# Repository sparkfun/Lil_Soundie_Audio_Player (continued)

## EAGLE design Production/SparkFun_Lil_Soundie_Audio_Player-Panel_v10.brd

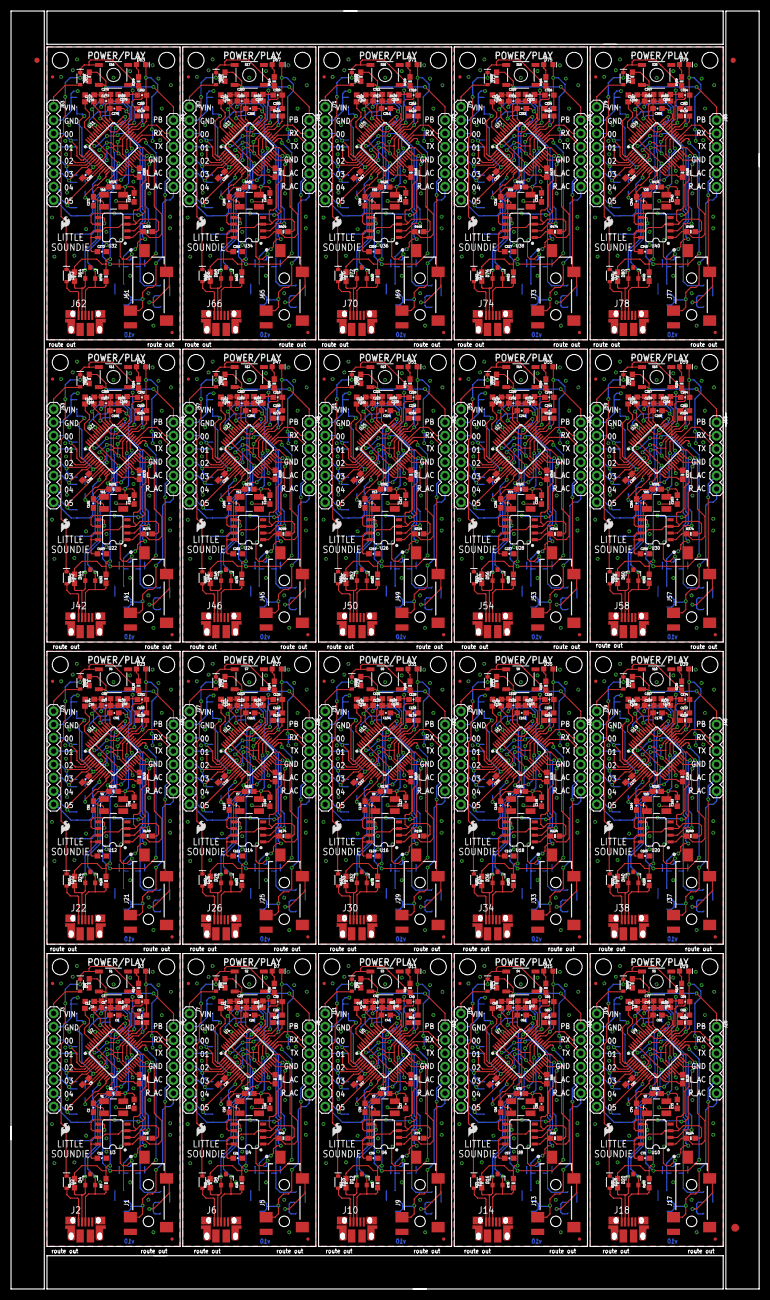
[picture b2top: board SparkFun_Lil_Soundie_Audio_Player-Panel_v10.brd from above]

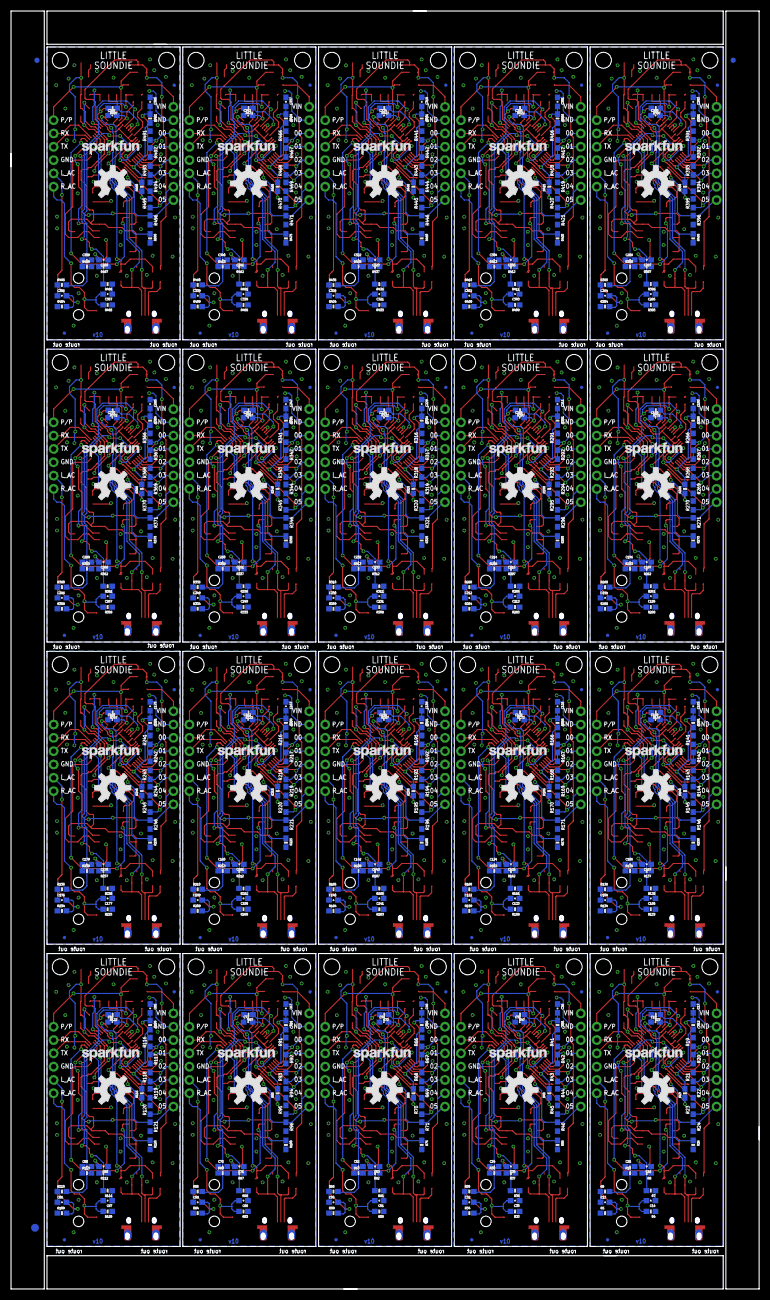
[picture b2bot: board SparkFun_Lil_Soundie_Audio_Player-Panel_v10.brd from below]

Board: 2 copper layers, 142.7 x 243.8 mm, 1286 parts (523 on the bottom side), 800 nets.

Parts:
C1, C2, C18, C20, C37, C38, C55, C56, C73, C74, C91, C92, C109, C110, C127, C128, C145, C146, C163, C164, C181, C182, C199, C200, C217, C218, C235, C236, C253, C254, C271, C272, C289, C290, C307, C308, C325, C326, C343, C344: 22pF; 0603-CAP
C3, C13, C14, C17, C23, C31, C32, C33, C41, C49, C50, C51, C59, C67, C68, C69, C77, C85, C86, C87, C95, C103, C104, C105, C113, C121, C122, C123, C131, C139, C140, C141, C149, C157, C158, C159, C167, C175, C176, C177, C185, C193, C194, C195, C203, C211, C212, C213, C221, C229, C230, C231, C239, C247, C248, C249, C257, C265, C266, C267, C275, C283, C284, C285, C293, C301, C302, C303, C311, C319, C320, C321, C329, C337, C338, C339, C347, C355, C356, C357: 10uF; 0603-CAP
C4, C5, C6, C7, C8, C9, C12, C21, C24, C25, C26, C27, C28, C29, C39, C42, C43, C44, C45, C46, C47, C57, C60, C61, C62, C63, C64, C65, C75, C78, C79, C80, C81, C82, C83, C93, C96, C97, C98, C99, C100, C101, C111, C114, C115, C116, C117, C118, C119, C129, C132, C133, C134, C135, C136, C137, C147, C150, C151, C152, C153, C154, C155, C165, C168, C169, C170, C171, C172, C173, C183, C186, C187, C188, C189, C190, C191, C201, C204, C205, C206, C207, C208, C209, C219, C222, C223, C224, C225, C226, C227, C237, C240, C241, C242, C243, C244, C245, C255, C258, C259, C260, C261, C262, C263, C273, C276, C277, C278, C279, C280, C281, C291, C294, C295, C296, C297, C298, C299, C309, C312, C313, C314, C315, C316, C317, C327, C330, C331, C332, C333, C334, C335, C345, C348, C349, C350, C351, C352, C353: 0.1uF; 0603-CAP
C10, C11, C22, C30, C40, C48, C58, C66, C76, C84, C94, C102, C112, C120, C130, C138, C148, C156, C166, C174, C184, C192, C202, C210, C220, C228, C238, C246, C256, C264, C274, C282, C292, C300, C310, C318, C328, C336, C346, C354: 1.0uF; 0603-CAP
C15, C16, C34, C35, C52, C53, C70, C71, C88, C89, C106, C107, C124, C125, C142, C143, C160, C161, C178, C179, C196, C197, C214, C215, C232, C233, C250, C251, C268, C269, C286, C287, C304, C305, C322, C323, C340, C341, C358, C359: 10nF; 0603-CAP
C19, C36, C54, C72, C90, C108, C126, C144, C162, C180, C198, C216, C234, C252, C270, C288, C306, C324, C342, C360: 47nF; 0603-CAP
D1, D2, D5, D6, D9, D10, D13, D14, D17, D18, D21, D22, D25, D26, D29, D30, D33, D34, D37, D38, D41, D42, D45, D46, D49, D50, D53, D54, D57, D58, D61, D62, D65, D66, D69, D70, D73, D74, D77, D78: 1A/23V/620mV; SOD-323
D3, D7, D11, D15, D19, D23, D27, D31, D35, D39, D43, D47, D51, D55, D59, D63, D67, D71, D75, D79: RED; LED-0603
D4, D8, D12, D16, D20, D24, D28, D32, D36, D40, D44, D48, D52, D56, D60, D64, D68, D72, D76, D80: PESD1CAN; SOT23-3
E$1, E$2, E$6, E$7: FIDUCIAL-1X2
E$3, E$4: FIDUCIAL-1.5X3
FD1, FD2, FD3, FD4, FD5, FD6, FD7, FD8, FD9, FD10, FD11, FD12, FD13, FD14, FD15, FD16, FD17, FD18, FD19, FD20, FD21, FD22, FD23, FD24, FD25, FD26, FD27, FD28, FD29, FD30, FD31, FD32, FD33, FD34, FD35, FD36, FD37, FD38, FD39, FD40, FD41, FD42, FD43, FD44, FD45, FD46, FD47, FD48, FD49, FD50, FD51, FD52, FD53, FD54, FD55, FD56, FD57, FD58, FD59, FD60, FD61, FD62, FD63, FD64, FD65, FD66, FD67, FD68, FD69, FD70, FD71, FD72, FD73, FD74, FD75, FD76, FD77, FD78, FD79, FD80: FIDUCIALUFIDUCIAL; FIDUCIAL-MICRO
H1, H2, H3, H4, H5, H6, H7, H8, H9, H10, H11, H12, H13, H14, H15, H16, H17, H18, H19, H20, H21, H22, H23, H24, H25, H26, H27, H28, H29, H30, H31, H32, H33, H34, H35, H36, H37, H38, H39, H40: STAND-OFFTIGHT; STAND-OFF-TIGHT
J1, J5, J9, J13, J17, J21, J25, J29, J33, J37, J41, J45, J49, J53, J57, J61, J65, J69, J73, J77: Audio Jack; AUDIO-JACK-3.5MM-SMD
J2, J6, J10, J14, J18, J22, J26, J30, J34, J38, J42, J46, J50, J54, J58, J62, J66, J70, J74, J78: AMP FCI 10103594-0001LF; USB-MICROB-PTH
J3, J7, J11, J15, J19, J23, J27, J31, J35, J39, J43, J47, J51, J55, J59, J63, J67, J71, J75, J79: 1X08
J4, J8, J12, J16, J20, J24, J28, J32, J36, J40, J44, J48, J52, J56, J60, J64, J68, J72, J76, J80: 1X06
LOGO1, LOGO3, LOGO5, LOGO7, LOGO9, LOGO11, LOGO13, LOGO15, LOGO17, LOGO19, LOGO21, LOGO23, LOGO25, LOGO27, LOGO29, LOGO31, LOGO33, LOGO35, LOGO37, LOGO39: OSHW-LOGOL; OSHW-LOGO-L
LOGO2, LOGO4, LOGO6, LOGO8, LOGO10, LOGO12, LOGO14, LOGO16, LOGO18, LOGO20, LOGO22, LOGO24, LOGO26, LOGO28, LOGO30, LOGO32, LOGO34, LOGO36, LOGO38, LOGO40: SFE_LOGO_NAME.1_INCH; SFE_LOGO_NAME_.1
R1, R2, R3, R9, R15, R16, R28, R30, R51, R52, R53, R55, R76, R77, R78, R80, R101, R102, R103, R105, R126, R127, R128, R130, R151, R152, R153, R155, R176, R177, R178, R180, R201, R202, R203, R205, R226, R227, R228, R230, R251, R252, R253, R255, R276, R277, R278, R280, R301, R302, R303, R305, R326, R327, R328, R330, R351, R352, R353, R355, R376, R377, R378, R380, R401, R402, R403, R405, R426, R427, R428, R430, R451, R452, R453, R455, R476, R477, R478, R480: 1M; 0603-RES
R4, R5, R33, R34, R58, R59, R83, R84, R108, R109, R133, R134, R158, R159, R183, R184, R208, R209, R233, R234, R258, R259, R283, R284, R308, R309, R333, R334, R358, R359, R383, R384, R408, R409, R433, R434, R458, R459, R483, R484: 10K; 0603-RES
R6, R7, R35, R36, R60, R61, R85, R86, R110, R111, R135, R136, R160, R161, R185, R186, R210, R211, R235, R236, R260, R261, R285, R286, R310, R311, R335, R336, R360, R361, R385, R386, R410, R411, R435, R436, R460, R461, R485, R486: 470; 0603-RES
R8, R10, R37, R38, R62, R63, R87, R88, R112, R113, R137, R138, R162, R163, R187, R188, R212, R213, R237, R238, R262, R263, R287, R288, R312, R313, R337, R338, R362, R363, R387, R388, R412, R413, R437, R438, R462, R463, R487, R488: 20; 0603-RES
R11, R12, R13, R18, R25, R26, R29, R31, R40, R48, R49, R50, R54, R56, R65, R73, R74, R75, R79, R81, R90, R98, R99, R100, R104, R106, R115, R123, R124, R125, R129, R131, R140, R148, R149, R150, R154, R156, R165, R173, R174, R175, R179, R181, R190, R198, R199, R200, R204, R206, R215, R223, R224, R225, R229, R231, R240, R248, R249, R250, R254, R256, R265, R273, R274, R275, R279, R281, R290, R298, R299, R300, R304, R306, R315, R323, R324, R325, R329, R331, R340, R348, R349, R350, R354, R356, R365, R373, R374, R375, R379, R381, R390, R398, R399, R400, R404, R406, R415, R423, R424, R425, R429, R431, R440, R448, R449, R450, R454, R456, R465, R473, R474, R475, R479, R481, R490, R498, R499, R500: 100k; 0603-RES
R14, R39, R64, R89, R114, R139, R164, R189, R214, R239, R264, R289, R314, R339, R364, R389, R414, R439, R464, R489: 180; 0603-RES
R17, R32, R57, R82, R107, R132, R157, R182, R207, R232, R257, R282, R307, R332, R357, R382, R407, R432, R457, R482: 150K; 0603-RES
R19, R20, R21, R22, R23, R24, R41, R42, R43, R44, R45, R46, R66, R67, R68, R69, R70, R71, R91, R92, R93, R94, R95, R96, R116, R117, R118, R119, R120, R121, R141, R142, R143, R144, R145, R146, R166, R167, R168, R169, R170, R171, R191, R192, R193, R194, R195, R196, R216, R217, R218, R219, R220, R221, R241, R242, R243, R244, R245, R246, R266, R267, R268, R269, R270, R271, R291, R292, R293, R294, R295, R296, R316, R317, R318, R319, R320, R321, R341, R342, R343, R344, R345, R346, R366, R367, R368, R369, R370, R371, R391, R392, R393, R394, R395, R396, R416, R417, R418, R419, R420, R421, R441, R442, R443, R444, R445, R446, R466, R467, R468, R469, R470, R471, R491, R492, R493, R494, R495, R496: 100k; 0603
R27, R47, R72, R97, R122, R147, R172, R197, R222, R247, R272, R297, R322, R347, R372, R397, R422, R447, R472, R497: 10; 0603-RES
S1, S2, S3, S4, S5, S6, S7, S8, S9, S10, S11, S12, S13, S14, S15, S16, S17, S18, S19, S20: SWITCH-MOMENTARY-2SMD; TACTILE-SWITCH-SMD
U1, U2, U5, U7, U9, U11, U13, U15, U17, U19, U21, U23, U25, U27, U29, U31, U33, U35, U37, U39: VS1000D; LQFP-48
U3, U4, U6, U8, U10, U12, U14, U16, U18, U20, U22, U24, U26, U28, U30, U32, U34, U36, U38, U40: 4MB Flash; SO08
U$1, U$2, U$3, U$4, U$5, U$6, U$7, U$8, U$9, U$10, U$11, U$12, U$13, U$14, U$15, U$16, U$17, U$18, U$19, U$20: SFE_LOGO_FLAME_.1
Y1, Y2, Y3, Y4, Y5, Y6, Y7, Y8, Y9, Y10, Y11, Y12, Y13, Y14, Y15, Y16, Y17, Y18, Y19, Y20: 12MHz; CRYSTAL-SMD-5X3

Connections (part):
AVDD: C3.1, C4.1, C5.1, C6.1, R2.2, R3.2, U2.34, U2.39, U2.44, U2.46
AVDD1: C23.1, C24.1, C25.1, C26.1, R16.2, R28.2, U1.34, U1.39, U1.44, U1.46
AVDD2: C41.1, C42.1, C43.1, C44.1, R52.2, R53.2, U5.34, U5.39, U5.44, U5.46
AVDD3: C59.1, C60.1, C61.1, C62.1, R77.2, R78.2, U7.34, U7.39, U7.44, U7.46
AVDD4: C77.1, C78.1, C79.1, C80.1, R102.2, R103.2, U9.34, U9.39, U9.44, U9.46
AVDD5: C95.1, C96.1, C97.1, C98.1, R127.2, R128.2, U11.34, U11.39, U11.44, U11.46
AVDD6: C113.1, C114.1, C115.1, C116.1, R152.2, R153.2, U13.34, U13.39, U13.44, U13.46
AVDD7: C131.1, C132.1, C133.1, C134.1, R177.2, R178.2, U15.34, U15.39, U15.44, U15.46
AVDD8: C149.1, C150.1, C151.1, C152.1, R202.2, R203.2, U17.34, U17.39, U17.44, U17.46
AVDD9: C167.1, C168.1, C169.1, C170.1, R227.2, R228.2, U19.34, U19.39, U19.44, U19.46
AVDD10: C185.1, C186.1, C187.1, C188.1, R252.2, R253.2, U21.34, U21.39, U21.44, U21.46
AVDD11: C203.1, C204.1, C205.1, C206.1, R277.2, R278.2, U23.34, U23.39, U23.44, U23.46
AVDD12: C221.1, C222.1, C223.1, C224.1, R302.2, R303.2, U25.34, U25.39, U25.44, U25.46
AVDD13: C239.1, C240.1, C241.1, C242.1, R327.2, R328.2, U27.34, U27.39, U27.44, U27.46
AVDD14: C257.1, C258.1, C259.1, C260.1, R352.2, R353.2, U29.34, U29.39, U29.44, U29.46
AVDD15: C275.1, C276.1, C277.1, C278.1, R377.2, R378.2, U31.34, U31.39, U31.44, U31.46
AVDD16: C293.1, C294.1, C295.1, C296.1, R402.2, R403.2, U33.34, U33.39, U33.44, U33.46
AVDD17: C311.1, C312.1, C313.1, C314.1, R427.2, R428.2, U35.34, U35.39, U35.44, U35.46
AVDD18: C329.1, C330.1, C331.1, C332.1, R452.2, R453.2, U37.34, U37.39, U37.44, U37.46
AVDD19: C347.1, C348.1, C349.1, C350.1, R477.2, R478.2, U39.34, U39.39, U39.44, U39.46
CVDD: C7.1, C10.1, R15.2, U2.32
CVDD1: C27.1, C30.1, R30.2, U1.32
CVDD2: C45.1, C48.1, R55.2, U5.32
CVDD3: C63.1, C66.1, R80.2, U7.32
CVDD4: C81.1, C84.1, R105.2, U9.32
CVDD5: C99.1, C102.1, R130.2, U11.32
CVDD6: C117.1, C120.1, R155.2, U13.32
CVDD7: C135.1, C138.1, R180.2, U15.32
CVDD8: C153.1, C156.1, R205.2, U17.32
CVDD9: C171.1, C174.1, R230.2, U19.32
CVDD10: C189.1, C192.1, R255.2, U21.32
CVDD11: C207.1, C210.1, R280.2, U23.32
CVDD12: C225.1, C228.1, R305.2, U25.32
CVDD13: C243.1, C246.1, R330.2, U27.32
CVDD14: C261.1, C264.1, R355.2, U29.32
CVDD15: C279.1, C282.1, R380.2, U31.32
CVDD16: C297.1, C300.1, R405.2, U33.32
CVDD17: C315.1, C318.1, R430.2, U35.32
CVDD18: C333.1, C336.1, R455.2, U37.32
CVDD19: C351.1, C354.1, R480.2, U39.32
DVDD: C8.1, C9.1, C12.1, R11.2, R12.2, R13.2, R18.1, R25.2, U2.7, U2.19, U2.30, U3.3, U3.7, U3.8
DVDD1: C21.1, C28.1, C29.1, R29.2, R31.2, R40.2, R48.1, R49.2, U1.7, U1.19, U1.30, U4.3, U4.7, U4.8
DVDD2: C39.1, C46.1, C47.1, R54.2, R56.2, R65.2, R73.1, R74.2, U5.7, U5.19, U5.30, U6.3, U6.7, U6.8
DVDD3: C57.1, C64.1, C65.1, R79.2, R81.2, R90.2, R98.1, R99.2, U7.7, U7.19, U7.30, U8.3, U8.7, U8.8
DVDD4: C75.1, C82.1, C83.1, R104.2, R106.2, R115.2, R123.1, R124.2, U9.7, U9.19, U9.30, U10.3, U10.7, U10.8
DVDD5: C93.1, C100.1, C101.1, R129.2, R131.2, R140.2, R148.1, R149.2, U11.7, U11.19, U11.30, U12.3, U12.7, U12.8
DVDD6: C111.1, C118.1, C119.1, R154.2, R156.2, R165.2, R173.1, R174.2, U13.7, U13.19, U13.30, U14.3, U14.7, U14.8
DVDD7: C129.1, C136.1, C137.1, R179.2, R181.2, R190.2, R198.1, R199.2, U15.7, U15.19, U15.30, U16.3, U16.7, U16.8
DVDD8: C147.1, C154.1, C155.1, R204.2, R206.2, R215.2, R223.1, R224.2, U17.7, U17.19, U17.30, U18.3, U18.7, U18.8
DVDD9: C165.1, C172.1, C173.1, R229.2, R231.2, R240.2, R248.1, R249.2, U19.7, U19.19, U19.30, U20.3, U20.7, U20.8
DVDD10: C183.1, C190.1, C191.1, R254.2, R256.2, R265.2, R273.1, R274.2, U21.7, U21.19, U21.30, U22.3, U22.7, U22.8
DVDD11: C201.1, C208.1, C209.1, R279.2, R281.2, R290.2, R298.1, R299.2, U23.7, U23.19, U23.30, U24.3, U24.7, U24.8
DVDD12: C219.1, C226.1, C227.1, R304.2, R306.2, R315.2, R323.1, R324.2, U25.7, U25.19, U25.30, U26.3, U26.7, U26.8
DVDD13: C237.1, C244.1, C245.1, R329.2, R331.2, R340.2, R348.1, R349.2, U27.7, U27.19, U27.30, U28.3, U28.7, U28.8
DVDD14: C255.1, C262.1, C263.1, R354.2, R356.2, R365.2, R373.1, R374.2, U29.7, U29.19, U29.30, U30.3, U30.7, U30.8
DVDD15: C273.1, C280.1, C281.1, R379.2, R381.2, R390.2, R398.1, R399.2, U31.7, U31.19, U31.30, U32.3, U32.7, U32.8
DVDD16: C291.1, C298.1, C299.1, R404.2, R406.2, R415.2, R423.1, R424.2, U33.7, U33.19, U33.30, U34.3, U34.7, U34.8
DVDD17: C309.1, C316.1, C317.1, R429.2, R431.2, R440.2, R448.1, R449.2, U35.7, U35.19, U35.30, U36.3, U36.7, U36.8
DVDD18: C327.1, C334.1, C335.1, R454.2, R456.2, R465.2, R473.1, R474.2, U37.7, U37.19, U37.30, U38.3, U38.7, U38.8
DVDD19: C345.1, C352.1, C353.1, R479.2, R481.2, R490.2, R498.1, R499.2, U39.7, U39.19, U39.30, U40.3, U40.7, U40.8
GBUF: R27.1, U2.43
GBUF1: R47.1, U1.43
GBUF2: R72.1, U5.43
GBUF3: R97.1, U7.43
GBUF4: R122.1, U9.43
GBUF5: R147.1, U11.43
GBUF6: R172.1, U13.43
GBUF7: R197.1, U15.43
GBUF8: R222.1, U17.43
GBUF9: R247.1, U19.43
GBUF10: R272.1, U21.43
GBUF11: R297.1, U23.43
GBUF12: R322.1, U25.43
GBUF13: R347.1, U27.43
GBUF14: R372.1, U29.43
GBUF15: R397.1, U31.43
GBUF16: R422.1, U33.43
GBUF17: R447.1, U35.43
GBUF18: R472.1, U37.43
GBUF19: R497.1, U39.43
GND: C1.1, C2.1, C3.2, C4.2, C5.2, C6.2, C7.2, C8.2, C9.2, C10.2, C11.2, C12.2, C15.2, C16.2, C17.1, C19.2, D3.C, D4.3, J1.SLEEVE, J2.GND, J3.2, J4.4, R4.1, R5.1, R15.1, R17.1, R19.2, R20.2, R21.2, R22.2, R23.2, R24.2, R26.2, U2.6, U2.8, U2.18, U2.31, U2.38, U2.41, U2.42, U2.48, U3.4
GND1: C18.1, C20.1, C21.2, C22.2, C23.2, C24.2, C25.2, C26.2, C27.2, C28.2, C29.2, C30.2, C31.1, C34.2, C35.2, C36.2, D7.C, D8.3, J5.SLEEVE, J6.GND, J7.2, J8.4, R30.1, R32.1, R33.1, R34.1, R41.2, R42.2, R43.2, R44.2, R45.2, R46.2, R50.2, U1.6, U1.8, U1.18, U1.31, U1.38, U1.41, U1.42, U1.48, U4.4
GND2: C37.1, C38.1, C39.2, C40.2, C41.2, C42.2, C43.2, C44.2, C45.2, C46.2, C47.2, C48.2, C49.1, C52.2, C53.2, C54.2, D11.C, D12.3, J9.SLEEVE, J10.GND, J11.2, J12.4, R55.1, R57.1, R58.1, R59.1, R66.2, R67.2, R68.2, R69.2, R70.2, R71.2, R75.2, U5.6, U5.8, U5.18, U5.31, U5.38, U5.41, U5.42, U5.48, U6.4
GND3: C55.1, C56.1, C57.2, C58.2, C59.2, C60.2, C61.2, C62.2, C63.2, C64.2, C65.2, C66.2, C67.1, C70.2, C71.2, C72.2, D15.C, D16.3, J13.SLEEVE, J14.GND, J15.2, J16.4, R80.1, R82.1, R83.1, R84.1, R91.2, R92.2, R93.2, R94.2, R95.2, R96.2, R100.2, U7.6, U7.8, U7.18, U7.31, U7.38, U7.41, U7.42, U7.48, U8.4
GND4: C73.1, C74.1, C75.2, C76.2, C77.2, C78.2, C79.2, C80.2, C81.2, C82.2, C83.2, C84.2, C85.1, C88.2, C89.2, C90.2, D19.C, D20.3, J17.SLEEVE, J18.GND, J19.2, J20.4, R105.1, R107.1, R108.1, R109.1, R116.2, R117.2, R118.2, R119.2, R120.2, R121.2, R125.2, U9.6, U9.8, U9.18, U9.31, U9.38, U9.41, U9.42, U9.48, U10.4
GND5: C91.1, C92.1, C93.2, C94.2, C95.2, C96.2, C97.2, C98.2, C99.2, C100.2, C101.2, C102.2, C103.1, C106.2, C107.2, C108.2, D23.C, D24.3, J21.SLEEVE, J22.GND, J23.2, J24.4, R130.1, R132.1, R133.1, R134.1, R141.2, R142.2, R143.2, R144.2, R145.2, R146.2, R150.2, U11.6, U11.8, U11.18, U11.31, U11.38, U11.41, U11.42, U11.48, U12.4
GND6: C109.1, C110.1, C111.2, C112.2, C113.2, C114.2, C115.2, C116.2, C117.2, C118.2, C119.2, C120.2, C121.1, C124.2, C125.2, C126.2, D27.C, D28.3, J25.SLEEVE, J26.GND, J27.2, J28.4, R155.1, R157.1, R158.1, R159.1, R166.2, R167.2, R168.2, R169.2, R170.2, R171.2, R175.2, U13.6, U13.8, U13.18, U13.31, U13.38, U13.41, U13.42, U13.48, U14.4
GND7: C127.1, C128.1, C129.2, C130.2, C131.2, C132.2, C133.2, C134.2, C135.2, C136.2, C137.2, C138.2, C139.1, C142.2, C143.2, C144.2, D31.C, D32.3, J29.SLEEVE, J30.GND, J31.2, J32.4, R180.1, R182.1, R183.1, R184.1, R191.2, R192.2, R193.2, R194.2, R195.2, R196.2, R200.2, U15.6, U15.8, U15.18, U15.31, U15.38, U15.41, U15.42, U15.48, U16.4
GND8: C145.1, C146.1, C147.2, C148.2, C149.2, C150.2, C151.2, C152.2, C153.2, C154.2, C155.2, C156.2, C157.1, C160.2, C161.2, C162.2, D35.C, D36.3, J33.SLEEVE, J34.GND, J35.2, J36.4, R205.1, R207.1, R208.1, R209.1, R216.2, R217.2, R218.2, R219.2, R220.2, R221.2, R225.2, U17.6, U17.8, U17.18, U17.31, U17.38, U17.41, U17.42, U17.48, U18.4
GND9: C163.1, C164.1, C165.2, C166.2, C167.2, C168.2, C169.2, C170.2, C171.2, C172.2, C173.2, C174.2, C175.1, C178.2, C179.2, C180.2, D39.C, D40.3, J37.SLEEVE, J38.GND, J39.2, J40.4, R230.1, R232.1, R233.1, R234.1, R241.2, R242.2, R243.2, R244.2, R245.2, R246.2, R250.2, U19.6, U19.8, U19.18, U19.31, U19.38, U19.41, U19.42, U19.48, U20.4
GND10: C181.1, C182.1, C183.2, C184.2, C185.2, C186.2, C187.2, C188.2, C189.2, C190.2, C191.2, C192.2, C193.1, C196.2, C197.2, C198.2, D43.C, D44.3, J41.SLEEVE, J42.GND, J43.2, J44.4, R255.1, R257.1, R258.1, R259.1, R266.2, R267.2, R268.2, R269.2, R270.2, R271.2, R275.2, U21.6, U21.8, U21.18, U21.31, U21.38, U21.41, U21.42, U21.48, U22.4
GND11: C199.1, C200.1, C201.2, C202.2, C203.2, C204.2, C205.2, C206.2, C207.2, C208.2, C209.2, C210.2, C211.1, C214.2, C215.2, C216.2, D47.C, D48.3, J45.SLEEVE, J46.GND, J47.2, J48.4, R280.1, R282.1, R283.1, R284.1, R291.2, R292.2, R293.2, R294.2, R295.2, R296.2, R300.2, U23.6, U23.8, U23.18, U23.31, U23.38, U23.41, U23.42, U23.48, U24.4
GND12: C217.1, C218.1, C219.2, C220.2, C221.2, C222.2, C223.2, C224.2, C225.2, C226.2, C227.2, C228.2, C229.1, C232.2, C233.2, C234.2, D51.C, D52.3, J49.SLEEVE, J50.GND, J51.2, J52.4, R305.1, R307.1, R308.1, R309.1, R316.2, R317.2, R318.2, R319.2, R320.2, R321.2, R325.2, U25.6, U25.8, U25.18, U25.31, U25.38, U25.41, U25.42, U25.48, U26.4
GND13: C235.1, C236.1, C237.2, C238.2, C239.2, C240.2, C241.2, C242.2, C243.2, C244.2, C245.2, C246.2, C247.1, C250.2, C251.2, C252.2, D55.C, D56.3, J53.SLEEVE, J54.GND, J55.2, J56.4, R330.1, R332.1, R333.1, R334.1, R341.2, R342.2, R343.2, R344.2, R345.2, R346.2, R350.2, U27.6, U27.8, U27.18, U27.31, U27.38, U27.41, U27.42, U27.48, U28.4
GND14: C253.1, C254.1, C255.2, C256.2, C257.2, C258.2, C259.2, C260.2, C261.2, C262.2, C263.2, C264.2, C265.1, C268.2, C269.2, C270.2, D59.C, D60.3, J57.SLEEVE, J58.GND, J59.2, J60.4, R355.1, R357.1, R358.1, R359.1, R366.2, R367.2, R368.2, R369.2, R370.2, R371.2, R375.2, U29.6, U29.8, U29.18, U29.31, U29.38, U29.41, U29.42, U29.48, U30.4
GND15: C271.1, C272.1, C273.2, C274.2, C275.2, C276.2, C277.2, C278.2, C279.2, C280.2, C281.2, C282.2, C283.1, C286.2, C287.2, C288.2, D63.C, D64.3, J61.SLEEVE, J62.GND, J63.2, J64.4, R380.1, R382.1, R383.1, R384.1, R391.2, R392.2, R393.2, R394.2, R395.2, R396.2, R400.2, U31.6, U31.8, U31.18, U31.31, U31.38, U31.41, U31.42, U31.48, U32.4
GND16: C289.1, C290.1, C291.2, C292.2, C293.2, C294.2, C295.2, C296.2, C297.2, C298.2, C299.2, C300.2, C301.1, C304.2, C305.2, C306.2, D67.C, D68.3, J65.SLEEVE, J66.GND, J67.2, J68.4, R405.1, R407.1, R408.1, R409.1, R416.2, R417.2, R418.2, R419.2, R420.2, R421.2, R425.2, U33.6, U33.8, U33.18, U33.31, U33.38, U33.41, U33.42, U33.48, U34.4
GND17: C307.1, C308.1, C309.2, C310.2, C311.2, C312.2, C313.2, C314.2, C315.2, C316.2, C317.2, C318.2, C319.1, C322.2, C323.2, C324.2, D71.C, D72.3, J69.SLEEVE, J70.GND, J71.2, J72.4, R430.1, R432.1, R433.1, R434.1, R441.2, R442.2, R443.2, R444.2, R445.2, R446.2, R450.2, U35.6, U35.8, U35.18, U35.31, U35.38, U35.41, U35.42, U35.48, U36.4
GND18: C325.1, C326.1, C327.2, C328.2, C329.2, C330.2, C331.2, C332.2, C333.2, C334.2, C335.2, C336.2, C337.1, C340.2, C341.2, C342.2, D75.C, D76.3, J73.SLEEVE, J74.GND, J75.2, J76.4, R455.1, R457.1, R458.1, R459.1, R466.2, R467.2, R468.2, R469.2, R470.2, R471.2, R475.2, U37.6, U37.8, U37.18, U37.31, U37.38, U37.41, U37.42, U37.48, U38.4
GND19: C343.1, C344.1, C345.2, C346.2, C347.2, C348.2, C349.2, C350.2, C351.2, C352.2, C353.2, C354.2, C355.1, C358.2, C359.2, C360.2, D79.C, D80.3, J77.SLEEVE, J78.GND, J79.2, J80.4, R480.1, R482.1, R483.1, R484.1, R491.2, R492.2, R493.2, R494.2, R495.2, R496.2, R500.2, U39.6, U39.8, U39.18, U39.31, U39.38, U39.41, U39.42, U39.48, U40.4
IO_00: J3.3, R19.1, U2.2
IO_01: J3.4, R20.1, U2.3
IO_02: J3.5, R21.1, U2.4
IO_03: J3.6, R22.1, U2.5
IO_04: J3.7, R23.1, U2.9
IO_05: J3.8, R24.1, U2.10
IO_06: R26.1, U2.11
IO_07: R13.1, U2.12
IO_08: J7.8, R46.1, U1.10
IO_09: J7.3, R41.1, U1.2
IO_10: J7.4, R42.1, U1.3
IO_11: J7.6, R44.1, U1.5
IO_12: J7.7, R45.1, U1.9
IO_13: R50.1, U1.11
IO_14: J7.5, R43.1, U1.4
IO_15: R40.1, U1.12
IO_16: J11.8, R71.1, U5.10
IO_17: J11.3, R66.1, U5.2
IO_18: J11.4, R67.1, U5.3
IO_19: J11.6, R69.1, U5.5
IO_20: J11.7, R70.1, U5.9
IO_21: R75.1, U5.11
IO_22: J11.5, R68.1, U5.4
IO_23: R65.1, U5.12
IO_24: J15.8, R96.1, U7.10
IO_25: J15.3, R91.1, U7.2
IO_26: J15.4, R92.1, U7.3
IO_27: J15.6, R94.1, U7.5
IO_28: J15.7, R95.1, U7.9
IO_29: R100.1, U7.11
IO_30: J15.5, R93.1, U7.4
IO_31: R90.1, U7.12
IO_32: J19.8, R121.1, U9.10
IO_33: J19.3, R116.1, U9.2
IO_34: J19.4, R117.1, U9.3
IO_35: J19.6, R119.1, U9.5
IO_36: J19.7, R120.1, U9.9
IO_37: R125.1, U9.11
IO_38: J19.5, R118.1, U9.4
IO_39: R115.1, U9.12
IO_40: J23.8, R146.1, U11.10
IO_41: J23.3, R141.1, U11.2
IO_42: J23.4, R142.1, U11.3
IO_43: J23.6, R144.1, U11.5
IO_44: J23.7, R145.1, U11.9
IO_45: R150.1, U11.11
IO_46: J23.5, R143.1, U11.4
IO_47: R140.1, U11.12
IO_48: J27.8, R171.1, U13.10
IO_49: J27.3, R166.1, U13.2
IO_50: J27.4, R167.1, U13.3
IO_51: J27.6, R169.1, U13.5
IO_52: J27.7, R170.1, U13.9
IO_53: R175.1, U13.11
IO_54: J27.5, R168.1, U13.4
IO_55: R165.1, U13.12
IO_56: J31.8, R196.1, U15.10
IO_57: J31.3, R191.1, U15.2
IO_58: J31.4, R192.1, U15.3
IO_59: J31.6, R194.1, U15.5
IO_60: J31.7, R195.1, U15.9
IO_61: R200.1, U15.11
IO_62: J31.5, R193.1, U15.4
IO_63: R190.1, U15.12
IO_64: J35.8, R221.1, U17.10
IO_65: J35.3, R216.1, U17.2
IO_66: J35.4, R217.1, U17.3
IO_67: J35.6, R219.1, U17.5
IO_68: J35.7, R220.1, U17.9
IO_69: R225.1, U17.11
IO_70: J35.5, R218.1, U17.4
IO_71: R215.1, U17.12
IO_72: J39.8, R246.1, U19.10
IO_73: J39.3, R241.1, U19.2
IO_74: J39.4, R242.1, U19.3
IO_75: J39.6, R244.1, U19.5
IO_76: J39.7, R245.1, U19.9
IO_77: R250.1, U19.11
IO_78: J39.5, R243.1, U19.4
IO_79: R240.1, U19.12
IO_80: J43.8, R271.1, U21.10
IO_81: J43.3, R266.1, U21.2
IO_82: J43.4, R267.1, U21.3
IO_83: J43.6, R269.1, U21.5
IO_84: J43.7, R270.1, U21.9
IO_85: R275.1, U21.11
IO_86: J43.5, R268.1, U21.4
IO_87: R265.1, U21.12
IO_88: J47.8, R296.1, U23.10
IO_89: J47.3, R291.1, U23.2
IO_90: J47.4, R292.1, U23.3
IO_91: J47.6, R294.1, U23.5
IO_92: J47.7, R295.1, U23.9
IO_93: R300.1, U23.11
IO_94: J47.5, R293.1, U23.4
IO_95: R290.1, U23.12
IO_96: J51.8, R321.1, U25.10
IO_97: J51.3, R316.1, U25.2
IO_98: J51.4, R317.1, U25.3
IO_99: J51.6, R319.1, U25.5
IO_100: J51.7, R320.1, U25.9
IO_101: R325.1, U25.11
IO_102: J51.5, R318.1, U25.4
IO_103: R315.1, U25.12
IO_104: J55.8, R346.1, U27.10
IO_105: J55.3, R341.1, U27.2
IO_106: J55.4, R342.1, U27.3
IO_107: J55.6, R344.1, U27.5
IO_108: J55.7, R345.1, U27.9
IO_109: R350.1, U27.11
IO_110: J55.5, R343.1, U27.4
IO_111: R340.1, U27.12
IO_112: J59.8, R371.1, U29.10
IO_113: J59.3, R366.1, U29.2
IO_114: J59.4, R367.1, U29.3
IO_115: J59.6, R369.1, U29.5
IO_116: J59.7, R370.1, U29.9
IO_117: R375.1, U29.11
IO_118: J59.5, R368.1, U29.4
IO_119: R365.1, U29.12
IO_120: J63.8, R396.1, U31.10
IO_121: J63.3, R391.1, U31.2
IO_122: J63.4, R392.1, U31.3
IO_123: J63.6, R394.1, U31.5
IO_124: J63.7, R395.1, U31.9
IO_125: R400.1, U31.11
IO_126: J63.5, R393.1, U31.4
IO_127: R390.1, U31.12
IO_128: J67.8, R421.1, U33.10
IO_129: J67.3, R416.1, U33.2
IO_130: J67.4, R417.1, U33.3
IO_131: J67.6, R419.1, U33.5
IO_132: J67.7, R420.1, U33.9
IO_133: R425.1, U33.11
IO_134: J67.5, R418.1, U33.4
IO_135: R415.1, U33.12
IO_136: J71.8, R446.1, U35.10
IO_137: J71.3, R441.1, U35.2
IO_138: J71.4, R442.1, U35.3
IO_139: J71.6, R444.1, U35.5
IO_140: J71.7, R445.1, U35.9
IO_141: R450.1, U35.11
IO_142: J71.5, R443.1, U35.4
IO_143: R440.1, U35.12
IO_144: J75.8, R471.1, U37.10
IO_145: J75.3, R466.1, U37.2
IO_146: J75.4, R467.1, U37.3
IO_147: J75.6, R469.1, U37.5
IO_148: J75.7, R470.1, U37.9
IO_149: R475.1, U37.11
IO_150: J75.5, R468.1, U37.4
IO_151: R465.1, U37.12
IO_152: J79.8, R496.1, U39.10
IO_153: J79.3, R491.1, U39.2
IO_154: J79.4, R492.1, U39.3
IO_155: J79.6, R494.1, U39.5
IO_156: J79.7, R495.1, U39.9
IO_157: R500.1, U39.11
IO_158: J79.5, R493.1, U39.4
IO_159: R490.1, U39.12
LEFT: R6.2, R10.2, U2.47
LEFT1: R35.2, R38.2, U1.47
LEFT2: R60.2, R63.2, U5.47
LEFT3: R85.2, R88.2, U7.47
LEFT4: R110.2, R113.2, U9.47
LEFT5: R135.2, R138.2, U11.47
LEFT6: R160.2, R163.2, U13.47
LEFT7: R185.2, R188.2, U15.47
LEFT8: R210.2, R213.2, U17.47
LEFT9: R235.2, R238.2, U19.47
LEFT10: R260.2, R263.2, U21.47
LEFT11: R285.2, R288.2, U23.47
LEFT12: R310.2, R313.2, U25.47
LEFT13: R335.2, R338.2, U27.47
LEFT14: R360.2, R363.2, U29.47
LEFT15: R385.2, R388.2, U31.47
LEFT16: R410.2, R413.2, U33.47
LEFT17: R435.2, R438.2, U35.47
LEFT18: R460.2, R463.2, U37.47
LEFT19: R485.2, R488.2, U39.47
L_AC: C13.2, J1.TIP, J4.5, R5.2
L_AC1: C32.2, J5.TIP, J8.5, R34.2
L_AC2: C50.2, J9.TIP, J12.5, R59.2
L_AC3: C68.2, J13.TIP, J16.5, R84.2
L_AC4: C86.2, J17.TIP, J20.5, R109.2
L_AC5: C104.2, J21.TIP, J24.5, R134.2
L_AC6: C122.2, J25.TIP, J28.5, R159.2
L_AC7: C140.2, J29.TIP, J32.5, R184.2
L_AC8: C158.2, J33.TIP, J36.5, R209.2
L_AC9: C176.2, J37.TIP, J40.5, R234.2
L_AC10: C194.2, J41.TIP, J44.5, R259.2
L_AC11: C212.2, J45.TIP, J48.5, R284.2
L_AC12: C230.2, J49.TIP, J52.5, R309.2
L_AC13: C248.2, J53.TIP, J56.5, R334.2
L_AC14: C266.2, J57.TIP, J60.5, R359.2
L_AC15: C284.2, J61.TIP, J64.5, R384.2
L_AC16: C302.2, J65.TIP, J68.5, R409.2
L_AC17: C320.2, J69.TIP, J72.5, R434.2
L_AC18: C338.2, J73.TIP, J76.5, R459.2
L_AC19: C356.2, J77.TIP, J80.5, R484.2
unnamed: C19.1, R27.2
unnamed: C13.1, R6.1
unnamed: C15.1, R10.1
unnamed: C11.1, U2.45
unnamed: C17.2, R12.1, U2.1
unnamed: D2.A, J2.VBUS
unnamed: C22.1, U1.45
unnamed: C14.1, R7.1
unnamed: D3.A, R14.2
unnamed: C16.1, R8.1
unnamed: C31.2, R31.1, U1.1
unnamed: D6.A, J6.VBUS
unnamed: D7.A, R39.2
unnamed: C32.1, R35.1
unnamed: C34.1, R38.1
unnamed: C33.1, R36.1
unnamed: C35.1, R37.1
unnamed: C36.1, R47.2
unnamed: C40.1, U5.45
unnamed: C49.2, R56.1, U5.1
unnamed: D10.A, J10.VBUS
unnamed: D11.A, R64.2
unnamed: C50.1, R60.1
unnamed: C52.1, R63.1
unnamed: C51.1, R61.1
unnamed: C53.1, R62.1
unnamed: C54.1, R72.2
unnamed: C58.1, U7.45
unnamed: C67.2, R81.1, U7.1
unnamed: D14.A, J14.VBUS
unnamed: D15.A, R89.2
unnamed: C68.1, R85.1
unnamed: C70.1, R88.1
unnamed: C69.1, R86.1
unnamed: C71.1, R87.1
unnamed: C72.1, R97.2
unnamed: C76.1, U9.45
unnamed: C85.2, R106.1, U9.1
unnamed: D18.A, J18.VBUS
unnamed: D19.A, R114.2
unnamed: C86.1, R110.1
unnamed: C88.1, R113.1
unnamed: C87.1, R111.1
unnamed: C89.1, R112.1
unnamed: C90.1, R122.2
unnamed: C94.1, U11.45
unnamed: C103.2, R131.1, U11.1
unnamed: D22.A, J22.VBUS
unnamed: D23.A, R139.2
unnamed: C104.1, R135.1
unnamed: C106.1, R138.1
unnamed: C105.1, R136.1
unnamed: C107.1, R137.1
unnamed: C108.1, R147.2
unnamed: C112.1, U13.45
unnamed: C121.2, R156.1, U13.1
unnamed: D26.A, J26.VBUS
unnamed: D27.A, R164.2
unnamed: C122.1, R160.1
unnamed: C124.1, R163.1
unnamed: C123.1, R161.1
unnamed: C125.1, R162.1
unnamed: C126.1, R172.2
unnamed: C130.1, U15.45
unnamed: C139.2, R181.1, U15.1
unnamed: D30.A, J30.VBUS
unnamed: D31.A, R189.2
unnamed: C140.1, R185.1
unnamed: C142.1, R188.1
unnamed: C141.1, R186.1
unnamed: C143.1, R187.1
unnamed: C144.1, R197.2
unnamed: C148.1, U17.45
unnamed: C157.2, R206.1, U17.1
unnamed: D34.A, J34.VBUS
unnamed: D35.A, R214.2
unnamed: C158.1, R210.1
unnamed: C160.1, R213.1
unnamed: C159.1, R211.1
unnamed: C161.1, R212.1
unnamed: C162.1, R222.2
unnamed: C166.1, U19.45
unnamed: C175.2, R231.1, U19.1
unnamed: D38.A, J38.VBUS
unnamed: D39.A, R239.2
unnamed: C176.1, R235.1
unnamed: C178.1, R238.1
unnamed: C177.1, R236.1
unnamed: C179.1, R237.1
unnamed: C180.1, R247.2
unnamed: C184.1, U21.45
unnamed: C193.2, R256.1, U21.1
unnamed: D42.A, J42.VBUS
unnamed: D43.A, R264.2
unnamed: C194.1, R260.1
unnamed: C196.1, R263.1
unnamed: C195.1, R261.1
unnamed: C197.1, R262.1
unnamed: C198.1, R272.2
unnamed: C202.1, U23.45
unnamed: C211.2, R281.1, U23.1
unnamed: D46.A, J46.VBUS
unnamed: D47.A, R289.2
unnamed: C212.1, R285.1
unnamed: C214.1, R288.1
unnamed: C213.1, R286.1
unnamed: C215.1, R287.1
unnamed: C216.1, R297.2
unnamed: C220.1, U25.45
unnamed: C229.2, R306.1, U25.1
unnamed: D50.A, J50.VBUS
unnamed: D51.A, R314.2
unnamed: C230.1, R310.1
unnamed: C232.1, R313.1
unnamed: C231.1, R311.1
unnamed: C233.1, R312.1
unnamed: C234.1, R322.2
unnamed: C238.1, U27.45
unnamed: C247.2, R331.1, U27.1
unnamed: D54.A, J54.VBUS
unnamed: D55.A, R339.2
unnamed: C248.1, R335.1
unnamed: C250.1, R338.1
unnamed: C249.1, R336.1
unnamed: C251.1, R337.1
unnamed: C252.1, R347.2
unnamed: C256.1, U29.45
unnamed: C265.2, R356.1, U29.1
unnamed: D58.A, J58.VBUS
unnamed: D59.A, R364.2
unnamed: C266.1, R360.1
unnamed: C268.1, R363.1
unnamed: C267.1, R361.1
unnamed: C269.1, R362.1
unnamed: C270.1, R372.2
unnamed: C274.1, U31.45
unnamed: C283.2, R381.1, U31.1
unnamed: D62.A, J62.VBUS
unnamed: D63.A, R389.2
unnamed: C284.1, R385.1
unnamed: C286.1, R388.1
unnamed: C285.1, R386.1
unnamed: C287.1, R387.1
unnamed: C288.1, R397.2
unnamed: C292.1, U33.45
unnamed: C301.2, R406.1, U33.1
unnamed: D66.A, J66.VBUS
unnamed: D67.A, R414.2
unnamed: C302.1, R410.1
unnamed: C304.1, R413.1
unnamed: C303.1, R411.1
unnamed: C305.1, R412.1
unnamed: C306.1, R422.2
unnamed: C310.1, U35.45
unnamed: C319.2, R431.1, U35.1
unnamed: D70.A, J70.VBUS
unnamed: D71.A, R439.2
unnamed: C320.1, R435.1
unnamed: C322.1, R438.1
unnamed: C321.1, R436.1
unnamed: C323.1, R437.1
unnamed: C324.1, R447.2
unnamed: C328.1, U37.45
unnamed: C337.2, R456.1, U37.1
unnamed: D74.A, J74.VBUS
unnamed: D75.A, R464.2
unnamed: C338.1, R460.1
unnamed: C340.1, R463.1
unnamed: C339.1, R461.1
unnamed: C341.1, R462.1
unnamed: C342.1, R472.2
unnamed: C346.1, U39.45
unnamed: C355.2, R481.1, U39.1
unnamed: D78.A, J78.VBUS
unnamed: D79.A, R489.2
unnamed: C356.1, R485.1
unnamed: C358.1, R488.1
unnamed: C357.1, R486.1
unnamed: C359.1, R487.1
unnamed: C360.1, R497.2
PWRBTN: J4.1, R17.2, S1.3, U2.37
PWRBTN1: J8.1, R32.2, S2.3, U1.37
PWRBTN2: J12.1, R57.2, S3.3, U5.37
PWRBTN3: J16.1, R82.2, S4.3, U7.37
PWRBTN4: J20.1, R107.2, S5.3, U9.37
PWRBTN5: J24.1, R132.2, S6.3, U11.37
PWRBTN6: J28.1, R157.2, S7.3, U13.37
PWRBTN7: J32.1, R182.2, S8.3, U15.37
PWRBTN8: J36.1, R207.2, S9.3, U17.37
PWRBTN9: J40.1, R232.2, S10.3, U19.37
PWRBTN10: J44.1, R257.2, S11.3, U21.37
PWRBTN11: J48.1, R282.2, S12.3, U23.37
PWRBTN12: J52.1, R307.2, S13.3, U25.37
PWRBTN13: J56.1, R332.2, S14.3, U27.37
PWRBTN14: J60.1, R357.2, S15.3, U29.37
PWRBTN15: J64.1, R382.2, S16.3, U31.37
PWRBTN16: J68.1, R407.2, S17.3, U33.37
PWRBTN17: J72.1, R432.2, S18.3, U35.37
PWRBTN18: J76.1, R457.2, S19.3, U37.37
PWRBTN19: J80.1, R482.2, S20.3, U39.37
RDY: R18.2, U2.13
RDY1: R48.2, U1.13
RDY2: R73.2, U5.13
RDY3: R98.2, U7.13
RDY4: R123.2, U9.13
RDY5: R148.2, U11.13
RDY6: R173.2, U13.13
RDY7: R198.2, U15.13
RDY8: R223.2, U17.13
RDY9: R248.2, U19.13
RDY10: R273.2, U21.13
RDY11: R298.2, U23.13
RDY12: R323.2, U25.13
RDY13: R348.2, U27.13
RDY14: R373.2, U29.13
RDY15: R398.2, U31.13
RDY16: R423.2, U33.13
RDY17: R448.2, U35.13
RDY18: R473.2, U37.13
RDY19: R498.2, U39.13
RIGHT: R7.2, R8.2, U2.40
RIGHT1: R36.2, R37.2, U1.40
RIGHT2: R61.2, R62.2, U5.40
RIGHT3: R86.2, R87.2, U7.40
RIGHT4: R111.2, R112.2, U9.40
RIGHT5: R136.2, R137.2, U11.40
RIGHT6: R161.2, R162.2, U13.40
RIGHT7: R186.2, R187.2, U15.40
RIGHT8: R211.2, R212.2, U17.40
RIGHT9: R236.2, R237.2, U19.40
RIGHT10: R261.2, R262.2, U21.40
RIGHT11: R286.2, R287.2, U23.40
RIGHT12: R311.2, R312.2, U25.40
RIGHT13: R336.2, R337.2, U27.40
RIGHT14: R361.2, R362.2, U29.40
RIGHT15: R386.2, R387.2, U31.40
RIGHT16: R411.2, R412.2, U33.40
RIGHT17: R436.2, R437.2, U35.40
RIGHT18: R461.2, R462.2, U37.40
RIGHT19: R486.2, R487.2, U39.40
RX: J4.2, U2.27
RX1: J8.2, U1.27
RX2: J12.2, U5.27
RX3: J16.2, U7.27
RX4: J20.2, U9.27
RX5: J24.2, U11.27
RX6: J28.2, U13.27
RX7: J32.2, U15.27
RX8: J36.2, U17.27
RX9: J40.2, U19.27
RX10: J44.2, U21.27
RX11: J48.2, U23.27
RX12: J52.2, U25.27
RX13: J56.2, U27.27
RX14: J60.2, U29.27
RX15: J64.2, U31.27
RX16: J68.2, U33.27
RX17: J72.2, U35.27
RX18: J76.2, U37.27
RX19: J80.2, U39.27
R_AC: C14.2, J1.RING, J4.6, R4.2
R_AC1: C33.2, J5.RING, J8.6, R33.2
R_AC2: C51.2, J9.RING, J12.6, R58.2
R_AC3: C69.2, J13.RING, J16.6, R83.2
R_AC4: C87.2, J17.RING, J20.6, R108.2
R_AC5: C105.2, J21.RING, J24.6, R133.2
R_AC6: C123.2, J25.RING, J28.6, R158.2
R_AC7: C141.2, J29.RING, J32.6, R183.2
R_AC8: C159.2, J33.RING, J36.6, R208.2
R_AC9: C177.2, J37.RING, J40.6, R233.2
R_AC10: C195.2, J41.RING, J44.6, R258.2
R_AC11: C213.2, J45.RING, J48.6, R283.2
R_AC12: C231.2, J49.RING, J52.6, R308.2
R_AC13: C249.2, J53.RING, J56.6, R333.2
R_AC14: C267.2, J57.RING, J60.6, R358.2
R_AC15: C285.2, J61.RING, J64.6, R383.2
R_AC16: C303.2, J65.RING, J68.6, R408.2
R_AC17: C321.2, J69.RING, J72.6, R433.2
R_AC18: C339.2, J73.RING, J76.6, R458.2
R_AC19: C357.2, J77.RING, J80.6, R483.2
SCLK: U2.23, U3.6
SCLK1: U1.23, U4.6
SCLK2: U5.23, U6.6
SCLK3: U7.23, U8.6
SCLK4: U9.23, U10.6
SCLK5: U11.23, U12.6
SCLK6: U13.23, U14.6
SCLK7: U15.23, U16.6
SCLK8: U17.23, U18.6
SCLK9: U19.23, U20.6
SCLK10: U21.23, U22.6
SCLK11: U23.23, U24.6
SCLK12: U25.23, U26.6
SCLK13: U27.23, U28.6
SCLK14: U29.23, U30.6
SCLK15: U31.23, U32.6
SCLK16: U33.23, U34.6
SCLK17: U35.23, U36.6
SCLK18: U37.23, U38.6
SCLK19: U39.23, U40.6
SI: U2.24, U3.2
SI1: U1.24, U4.2
SI2: U5.24, U6.2
SI3: U7.24, U8.2
SI4: U9.24, U10.2
SI5: U11.24, U12.2
SI6: U13.24, U14.2
SI7: U15.24, U16.2
SI8: U17.24, U18.2
SI9: U19.24, U20.2
SI10: U21.24, U22.2
SI11: U23.24, U24.2
SI12: U25.24, U26.2
SI13: U27.24, U28.2
SI14: U29.24, U30.2
SI15: U31.24, U32.2
SI16: U33.24, U34.2
SI17: U35.24, U36.2
SI18: U37.24, U38.2
SI19: U39.24, U40.2
SO: U2.25, U3.5
SO1: U1.25, U4.5
SO2: U5.25, U6.5
SO3: U7.25, U8.5
SO4: U9.25, U10.5
SO5: U11.25, U12.5
SO6: U13.25, U14.5
SO7: U15.25, U16.5
SO8: U17.25, U18.5
SO9: U19.25, U20.5
SO10: U21.25, U22.5
SO11: U23.25, U24.5
SO12: U25.25, U26.5
SO13: U27.25, U28.5
SO14: U29.25, U30.5
SO15: U31.25, U32.5
SO16: U33.25, U34.5
SO17: U35.25, U36.5
SO18: U37.25, U38.5
SO19: U39.25, U40.5
TX: J4.3, U2.26
TX1: J8.3, U1.26
TX2: J12.3, U5.26
TX3: J16.3, U7.26
TX4: J20.3, U9.26
TX5: J24.3, U11.26
TX6: J28.3, U13.26
TX7: J32.3, U15.26
TX8: J36.3, U17.26
TX9: J40.3, U19.26
TX10: J44.3, U21.26
TX11: J48.3, U23.26
TX12: J52.3, U25.26
TX13: J56.3, U27.26
TX14: J60.3, U29.26
TX15: J64.3, U31.26
TX16: J68.3, U33.26
TX17: J72.3, U35.26
TX18: J76.3, U37.26
TX19: J80.3, U39.26
USBN: D4.1, J2.D-, R2.1, U2.36
USBN1: D8.1, J6.D-, R16.1, U1.36
USBN2: D12.1, J10.D-, R52.1, U5.36
USBN3: D16.1, J14.D-, R77.1, U7.36
USBN4: D20.1, J18.D-, R102.1, U9.36
USBN5: D24.1, J22.D-, R127.1, U11.36
USBN6: D28.1, J26.D-, R152.1, U13.36
USBN7: D32.1, J30.D-, R177.1, U15.36
USBN8: D36.1, J34.D-, R202.1, U17.36
USBN9: D40.1, J38.D-, R227.1, U19.36
USBN10: D44.1, J42.D-, R252.1, U21.36
USBN11: D48.1, J46.D-, R277.1, U23.36
USBN12: D52.1, J50.D-, R302.1, U25.36
USBN13: D56.1, J54.D-, R327.1, U27.36
USBN14: D60.1, J58.D-, R352.1, U29.36
USBN15: D64.1, J62.D-, R377.1, U31.36
USBN16: D68.1, J66.D-, R402.1, U33.36
USBN17: D72.1, J70.D-, R427.1, U35.36
USBN18: D76.1, J74.D-, R452.1, U37.36
USBN19: D80.1, J78.D-, R477.1, U39.36
USBP: D4.2, J2.D+, R3.1, U2.35
USBP1: D8.2, J6.D+, R28.1, U1.35
USBP2: D12.2, J10.D+, R53.1, U5.35
USBP3: D16.2, J14.D+, R78.1, U7.35
USBP4: D20.2, J18.D+, R103.1, U9.35
USBP5: D24.2, J22.D+, R128.1, U11.35
USBP6: D28.2, J26.D+, R153.1, U13.35
USBP7: D32.2, J30.D+, R178.1, U15.35
USBP8: D36.2, J34.D+, R203.1, U17.35
USBP9: D40.2, J38.D+, R228.1, U19.35
USBP10: D44.2, J42.D+, R253.1, U21.35
USBP11: D48.2, J46.D+, R278.1, U23.35
USBP12: D52.2, J50.D+, R303.1, U25.35
USBP13: D56.2, J54.D+, R328.1, U27.35
USBP14: D60.2, J58.D+, R353.1, U29.35
USBP15: D64.2, J62.D+, R378.1, U31.35
USBP16: D68.2, J66.D+, R403.1, U33.35
USBP17: D72.2, J70.D+, R428.1, U35.35
USBP18: D76.2, J74.D+, R453.1, U37.35
USBP19: D80.2, J78.D+, R478.1, U39.35
VCC: D1.A, J3.1
VCC1: D5.A, J7.1
VCC2: D9.A, J11.1
VCC3: D13.A, J15.1
VCC4: D17.A, J19.1
VCC5: D21.A, J23.1
VCC6: D25.A, J27.1
VCC7: D29.A, J31.1
VCC8: D33.A, J35.1
VCC9: D37.A, J39.1
VCC10: D41.A, J43.1
VCC11: D45.A, J47.1
VCC12: D49.A, J51.1
VCC13: D53.A, J55.1
VCC14: D57.A, J59.1
VCC15: D61.A, J63.1
VCC16: D65.A, J67.1
VCC17: D69.A, J71.1
VCC18: D73.A, J75.1
VCC19: D77.A, J79.1
VHIGH: D1.C, D2.C, R14.1, S1.1, U2.33
VHIGH1: D5.C, D6.C, R39.1, S2.1, U1.33
VHIGH2: D9.C, D10.C, R64.1, S3.1, U5.33
VHIGH3: D13.C, D14.C, R89.1, S4.1, U7.33
VHIGH4: D17.C, D18.C, R114.1, S5.1, U9.33
VHIGH5: D21.C, D22.C, R139.1, S6.1, U11.33
VHIGH6: D25.C, D26.C, R164.1, S7.1, U13.33
VHIGH7: D29.C, D30.C, R189.1, S8.1, U15.33
VHIGH8: D33.C, D34.C, R214.1, S9.1, U17.33
VHIGH9: D37.C, D38.C, R239.1, S10.1, U19.33
VHIGH10: D41.C, D42.C, R264.1, S11.1, U21.33
VHIGH11: D45.C, D46.C, R289.1, S12.1, U23.33
VHIGH12: D49.C, D50.C, R314.1, S13.1, U25.33
VHIGH13: D53.C, D54.C, R339.1, S14.1, U27.33
VHIGH14: D57.C, D58.C, R364.1, S15.1, U29.33
VHIGH15: D61.C, D62.C, R389.1, S16.1, U31.33
VHIGH16: D65.C, D66.C, R414.1, S17.1, U33.33
VHIGH17: D69.C, D70.C, R439.1, S18.1, U35.33
VHIGH18: D73.C, D74.C, R464.1, S19.1, U37.33
VHIGH19: D77.C, D78.C, R489.1, S20.1, U39.33
XCS: R25.1, U2.22, U3.1
XCS1: R49.1, U1.22, U4.1
XCS2: R74.1, U5.22, U6.1
XCS3: R99.1, U7.22, U8.1
XCS4: R124.1, U9.22, U10.1
XCS5: R149.1, U11.22, U12.1
XCS6: R174.1, U13.22, U14.1
XCS7: R199.1, U15.22, U16.1
XCS8: R224.1, U17.22, U18.1
XCS9: R249.1, U19.22, U20.1
XCS10: R274.1, U21.22, U22.1
XCS11: R299.1, U23.22, U24.1
XCS12: R324.1, U25.22, U26.1
XCS13: R349.1, U27.22, U28.1
XCS14: R374.1, U29.22, U30.1
XCS15: R399.1, U31.22, U32.1
XCS16: R424.1, U33.22, U34.1
XCS17: R449.1, U35.22, U36.1
XCS18: R474.1, U37.22, U38.1
XCS19: R499.1, U39.22, U40.1
XTAL0: C2.2, R1.1, U2.29, Y1.1
XTAL1: C1.2, R1.2, U2.28, Y1.3
XTAL2: C18.2, R9.2, U1.28, Y2.3
XTAL3: C20.2, R9.1, U1.29, Y2.1
XTAL4: C37.2, R51.2, U5.28, Y3.3
XTAL5: C38.2, R51.1, U5.29, Y3.1
XTAL6: C55.2, R76.2, U7.28, Y4.3
XTAL7: C56.2, R76.1, U7.29, Y4.1
XTAL8: C73.2, R101.2, U9.28, Y5.3
XTAL9: C74.2, R101.1, U9.29, Y5.1
XTAL10: C91.2, R126.2, U11.28, Y6.3
XTAL11: C92.2, R126.1, U11.29, Y6.1
XTAL12: C109.2, R151.2, U13.28, Y7.3
XTAL13: C110.2, R151.1, U13.29, Y7.1
XTAL14: C127.2, R176.2, U15.28, Y8.3
XTAL15: C128.2, R176.1, U15.29, Y8.1
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
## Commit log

2017-12-08 Updated design: active high input pins. Cleaned up schematic and layout
2017-12-13 Fixed trace issue on IO7
2017-12-13 Updated per QC review
2017-12-13 Moving LED
2018-02-11 Add GPIO Control
2018-02-11 Add gitignore
2018-02-11 Rename Lil_Soundie
2018-02-11 Add WAV playback
2018-02-11 Add inverted data
2018-02-11 Add logging for playback
2018-02-11 Update gitignore
2018-02-11 Add fat12patch
2018-02-11 Initial code submission
2018-02-11 Turn off logging
2018-02-11 Reformat sucky code
2018-02-11 Add switch to turn on/off WAV playback
2018-02-11 Working GPIO control
2018-02-11 Make Lil_Sound the selected project
2018-02-11 Add required descriptor files for build
2018-02-11 Remove required descriptors from gitignore
2018-02-11 Update workspace descriptiong files
2018-02-11 Fix bug for mounting USB
2018-02-11 Remove prints so promming binary works
2018-02-20 Updating Silk
2018-02-20 Updated name
2018-02-22 Created panel v10
2018-03-03 Reformat code
2018-03-12 Adding Space for tutorial Projects
2018-03-31 Fix device hang on non-existent file
2018-04-06 Fix flash size
2018-04-23 Cleaning up Repo
2018-04-23 Updating ReadME
2018-04-27 Fixing default image
    Image link was broken.
